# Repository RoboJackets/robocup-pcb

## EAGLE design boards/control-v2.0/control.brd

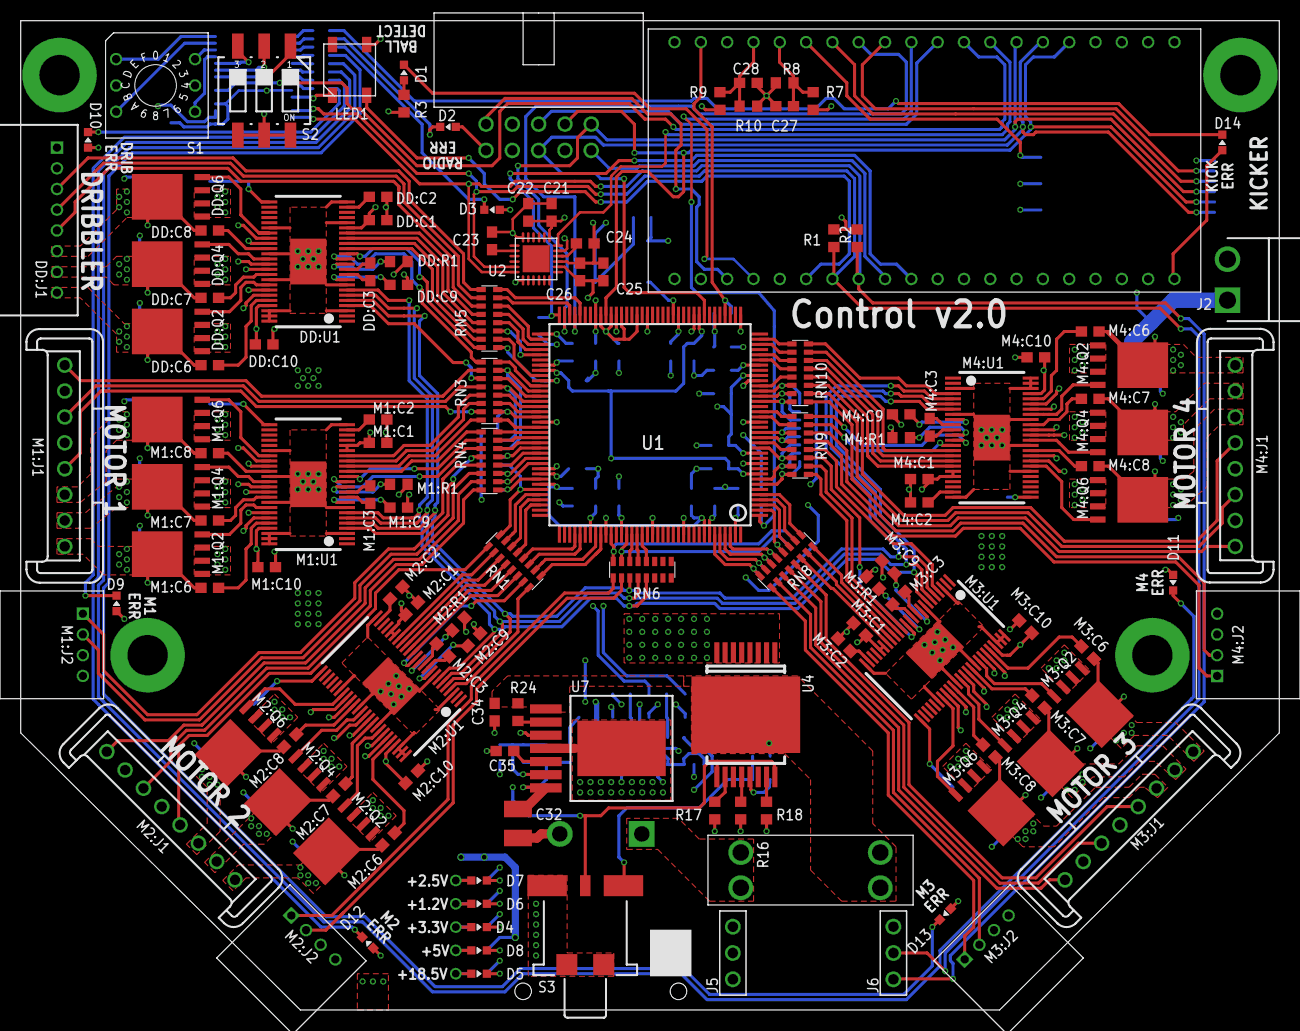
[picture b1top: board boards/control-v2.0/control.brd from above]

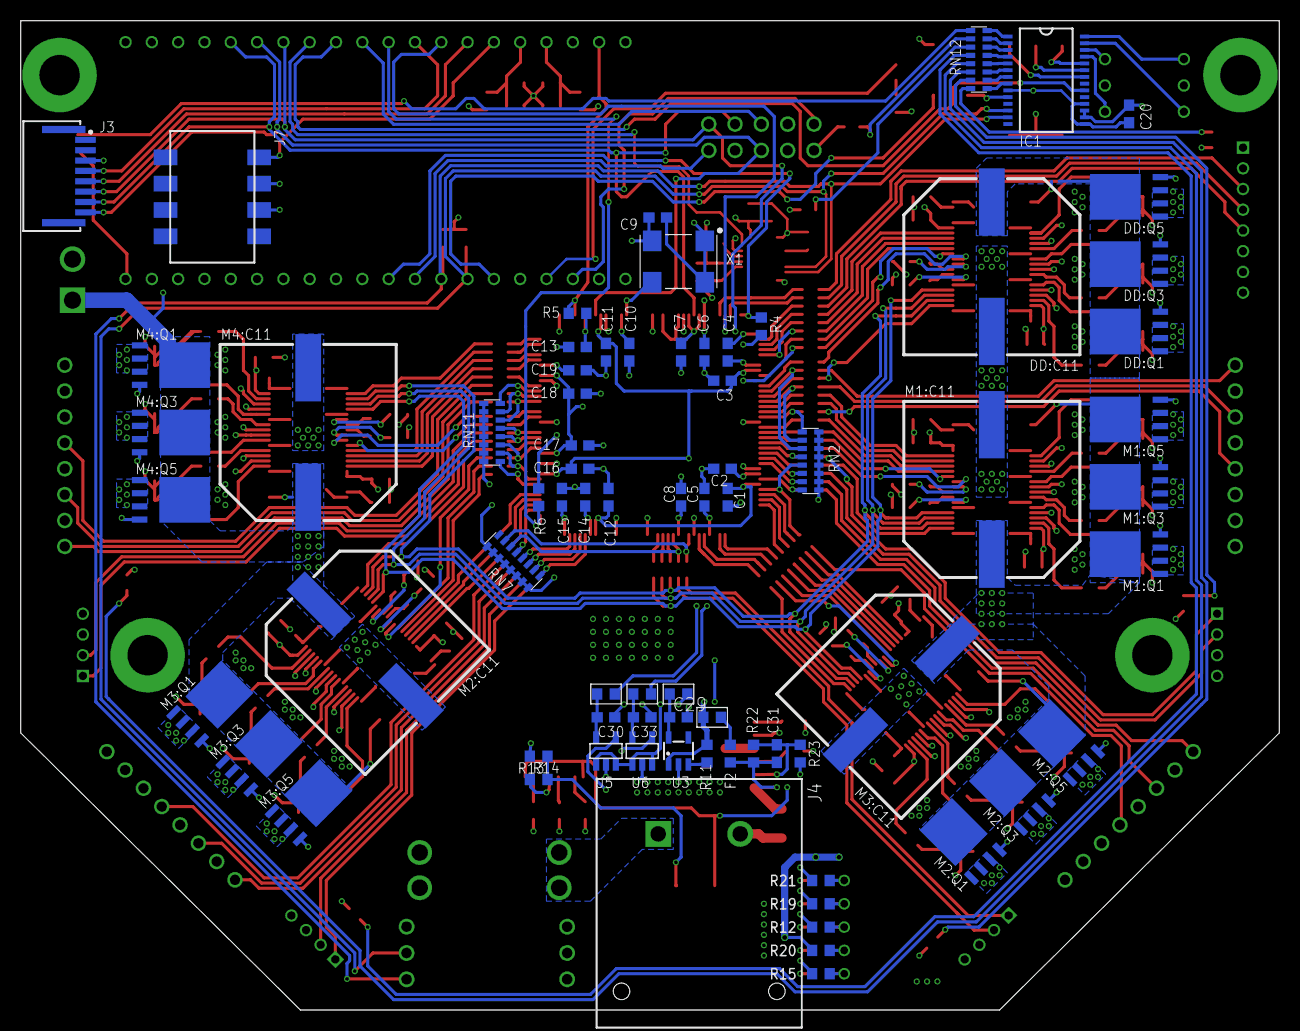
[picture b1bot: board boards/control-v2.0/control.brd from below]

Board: 4 copper layers, 121.5 x 95.5 mm, 206 parts (74 on the bottom side), 284 nets.

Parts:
C1, C2, C3, C4, C5, C6, C7, C8, C9, C10, C11, C12, C13, C14, C15, C16, C17, C18, C19, C20, C24, C27, C28: 0.1uF; C0603
C21, C22, C26: 0.47uF; C0603
C23: 2200pF; C0603
C25: 10000pF; C0603
C29, C30, C33: 1uF; C0603
C31: 0.022uF; C0603
C32: LMK325ABJ107MM-P; C1210
C34: GRM188R6YA106MA73D; C0603
C35: 0.1uF 50V; C0603
D1: BLUE; CHIP-LED0603
D2, D3, D9, D10, D11, D12, D13, D14: RED; CHIP-LED0603
D4, D5, D6, D7, D8: GREEN; CHIP-LED0603
DD:C1, DD:C2: 1uF; C0603
DD:C3: 0.022uF 50V; C0603
DD:C6, DD:C7, DD:C8, DD:C10: 0.1uF 50V; C0603
DD:C9: 2.2uF 50V; C0603
DD:C11: EEE-FK1H102AM; PANASONIC_J16
DD:J1: 8-PIN_2MM-H; 2MM-8-H
DD:Q1, DD:Q2, DD:Q3, DD:Q4, DD:Q5, DD:Q6: IRFH7545; PQFN_5X6_E
DD:R1: 10k; R0603
DD:U1: DRV8303DCA; TSSOP-48_PAD
F1: 30A; 3557-2
F2: 0603L075SLYR; F0603
IC1: MCP23017-E/SS; SSOP-28
J1: SBH11-PBPC-D05-RA; SBH11-*-D05-RA
J2: B2PS-VH(LF)(SN); B2PS-CENTERED
J3: HFW8R-1ST
J4: DF22-2; DF22-2-H
J5, J6: 3-PIN-HEADER
J7: 147721-3
KIT1: MBED_NXP_LPC1768; MBED-KIT
LED1: WS2812B; 5050
M1:C1, M1:C2, M2:C1, M2:C2, M3:C1, M3:C2, M4:C1, M4:C2: 1uF; C0603
M1:C3, M2:C3, M3:C3, M4:C3: 0.022uF 50V; C0603
M1:C6, M1:C7, M1:C8, M1:C10, M2:C6, M2:C7, M2:C8, M2:C10, M3:C6, M3:C7, M3:C8, M3:C10, M4:C6, M4:C7, M4:C8, M4:C10: 0.1uF 50V; C0603
M1:C9, M2:C9, M3:C9, M4:C9: 2.2uF 50V; C0603
M1:C11, M2:C11, M3:C11, M4:C11: EEE-FK1H102AM; PANASONIC_J16
M1:J1, M2:J1, M3:J1, M4:J1: MKS-1658
M1:J2, M2:J2, M3:J2, M4:J2: 4-PIN_2MM-H; 2MM-4-H
M1:Q1, M1:Q2, M1:Q3, M1:Q4, M1:Q5, M1:Q6, M2:Q1, M2:Q2, M2:Q3, M2:Q4, M2:Q5, M2:Q6, M3:Q1, M3:Q2, M3:Q3, M3:Q4, M3:Q5, M3:Q6, M4:Q1, M4:Q2, M4:Q3, M4:Q4, M4:Q5, M4:Q6: IRFH7545; PQFN_5X6_E
M1:R1, M2:R1, M3:R1, M4:R1: 10k; R0603
M1:U1, M2:U1, M3:U1, M4:U1: DRV8303DCA; TSSOP-48_PAD
R1, R2, R5, R6: 4.7k; R0603
R3, R4, R12, R19, R21: 330; R0603
R7: 68k; R0603
R8, R9, R10, R11, R16: 10k; R0603
R13: 270k; R0603
R14, R24: 100k; R0603
R15, R17, R18, R20: 1k; R0603
R22: 34k; R0603
R23: 6.49k; R0603
RN1, RN3, RN4, RN5, RN6, RN8, RN9, RN10: 330; RA-8_2506
RN2, RN7, RN11, RN12: RA-8_2506
S1: 94HCB16T; HEX
S2: 219-03; CTS-219-03
S3: 34EWMSP12M6RT
SB1, SB2, SB3, SB4: SOLDERBRIDGESB0603; SB0603
U1: XC3S250E-4TQG144C; TQFP144
U2: MPU-6050; QFN-24-4MM2
U3: TLV70233DBVR; SOT-23-5
U4: VND5E006ASPTR-E; POWERSO-16
U5: MCP1824T-1202E/OT; SOT-23-5
U6: MCP1824T-2502E/OT; SOT-23-5
U7: LMZ14201; TO-PMOD-7
X1: ASV-18.432MHZ-EJ-T; ASV

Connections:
1.2V-LED: R19.1, U5.4
1.2V-LED-PRE: D6.A, R19.2
2.5V-LED: R21.1, U6.4
2.5V-LED-PRE: D7.A, R21.2
3.3V-EN: R11.1, U3.3
3.3V-LED-PRE: D4.A, R12.1
5V-LED-PRE: D8.A, R20.2
18.5V-LED-PRE: D5.A, R15.1
!CS!-FPGA: KIT1.P$13, U1.69
!CS!-KICK: J3.5, KIT1.P$14
!CS!-RADIO: J1.10, KIT1.P$29
!RST!-KICK: J3.4, KIT1.P$12
!RST!-RADIO: J1.5, KIT1.P$23
+1.2V: C3.1, C5.1, C11.1, C16.1, SB2.2, U1.9, U1.45, U1.80, U1.115
+1.2V-PRE: C30.1, SB2.1, U5.5
+2.5V: C1.1, C6.1, C12.1, C19.1, R4.2, R6.2, SB4.2, U1.30, U1.65, U1.102, U1.137
+2.5V-PRE: C33.1, SB4.1, U6.5
+3.3V: C2.1, C4.1, C7.1, C8.1, C9.1, C10.1, C13.1, C14.1, C15.1, C17.1, C18.1, C20.1, C21.1, C22.1, C25.1, C26.1, D2.A, D3.A, D9.A, D10.A, D11.A, D12.A, D13.A, D14.A, DD:C1.1, DD:C10.1, DD:J1.2, DD:R1.1, DD:U1.19, DD:U1.45, IC1.9, IC1.15, IC1.18, J1.6, J5.2, J7.3, KIT1.VOUT, LED1.1, M1:C1.1, M1:C10.1, M1:R1.1, M1:U1.19, M1:U1.20, M1:U1.45, M2:C1.1, M2:C10.1, M2:R1.1, M2:U1.19, M2:U1.20, M2:U1.45, M3:C1.1, M3:C10.1, M3:R1.1, M3:U1.19, M3:U1.20, M3:U1.45, M4:C1.1, M4:C10.1, M4:R1.1, M4:U1.19, M4:U1.20, M4:U1.45, R1.2, R2.2, R3.2, R5.1, R12.2, SB1.2, U1.13, U1.28, U1.42, U1.49, U1.57, U1.60, U1.62, U1.64, U1.79, U1.100, U1.121, U1.138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
+3.3V-PRE: C29.1, SB1.1, U3.5
+5V: KIT1.VIN, KIT1.VU, M1:J1.4, M1:J2.4, M2:J1.4, M2:J2.4, M3:J1.4, M3:J2.4, M4:J1.4, M4:J2.4, R9.1, R11.2, R20.1, SB3.2, U3.1
+5V-FUSE: C31.1, C32.1, F2.1, R22.2, U7.7
+5V-PRE: F2.2, SB3.1
+18.5V: DD:C11.+, DD:Q1.5678, DD:Q3.5678, DD:Q5.5678, DD:U1.25, J2.1, M1:C11.+, M1:Q1.5678, M1:Q3.5678, M1:Q5.5678, M1:U1.25, M2:C11.+, M2:Q1.5678, M2:Q3.5678, M2:Q5.5678, M2:U1.25, M3:C11.+, M3:Q1.5678, M3:Q3.5678, M3:Q5.5678, M3:U1.25, M4:C11.+, M4:Q1.5678, M4:Q3.5678, M4:Q5.5678, M4:U1.25, R7.1, R15.2, U4.1, U4.2, U4.3, U4.4, U4.5, U4.6, U4.7, U4.8
BALL-DETECT: J7.1, KIT1.P$15
CPOUT: C23.1, U2.20
CS1: R17.2, U4.10
CS2: R18.2, U4.15
CS-DIS: R16.2, U4.12
DD-!CS: DD:U1.4, RN3.11
DD-A-H: DD:U1.13, RN3.9
DD-A-L: DD:U1.14, RN5.16
DD-B-H: DD:U1.15, RN5.15
DD-B-L: DD:U1.16, RN5.14
DD-C-H: DD:U1.17, RN5.13
DD-C-L: DD:U1.18, RN5.12
DD-H1: DD:J1.5, RN5.11
DD-H2: DD:J1.4, RN5.10
DD-H3: DD:J1.3, RN5.9
DD:AVDD: DD:C2.1, DD:U1.23
DD:BST-A: DD:C6.1, DD:U1.44
DD:BST-B: DD:C7.1, DD:U1.39
DD:BST-C: DD:C8.1, DD:U1.34
DD:CP1: DD:C3.1, DD:U1.10
DD:CP2: DD:C3.2, DD:U1.11
DD:EN-GATE: DD:R1.2, DD:U1.12
DD:GH-A: DD:Q1.4, DD:U1.43
DD:GH-B: DD:Q3.4, DD:U1.38
DD:GH-C: DD:Q5.4, DD:U1.33
DD:GL-A: DD:Q2.4, DD:U1.41
DD:GL-B: DD:Q4.4, DD:U1.36
DD:GL-C: DD:Q6.4, DD:U1.31
DD:GVDD: DD:C9.1, DD:U1.9
DD:PHASE-A: DD:C6.2, DD:J1.8, DD:Q1.1, DD:Q1.2, DD:Q1.3, DD:Q2.5678, DD:U1.42
DD:PHASE-B: DD:C7.2, DD:J1.7, DD:Q3.1, DD:Q3.2, DD:Q3.3, DD:Q4.5678, DD:U1.37
DD:PHASE-C: DD:C8.2, DD:J1.6, DD:Q5.1, DD:Q5.2, DD:Q5.3, DD:Q6.5678, DD:U1.32
DIP-1: IC1.22, S2.1
DIP-2: IC1.23, S2.2
DIP-3: IC1.24, S2.3
EN-PWR: S3.2, U4.9, U4.16, U7.3
EN-PWR-PRE: R13.1, R14.2, S3.1
FB: C31.2, R22.1, R23.2, U7.6
FPGA-CLK: U1.50, X1.3
FPGA-DONE: KIT1.P$30, R4.1, U1.72
FPGA-INIT: KIT1.P$19, R5.2, U1.40
FPGA-PROG: KIT1.P$11, R6.1, U1.1
GND: C1.2, C2.2, C3.2, C4.2, C5.2, C6.2, C7.2, C8.2, C9.2, C10.2, C11.2, C12.2, C13.2, C14.2, C15.2, C16.2, C17.2, C18.2, C19.2, C20.2, C21.2, C22.2, C23.2, C24.2, C25.2, C26.2, C27.2, C28.2, C29.2, C30.2, C32.2, C33.2, C34.2, C35.2, D4.C, D5.C, D6.C, D7.C, D8.C, DD:C1.2, DD:C2.2, DD:C9.2, DD:C10.2, DD:C11.-, DD:J1.1, DD:Q2.1, DD:Q2.2, DD:Q2.3, DD:Q4.1, DD:Q4.2, DD:Q4.3, DD:Q6.1, DD:Q6.2, DD:Q6.3, DD:U1.3, DD:U1.8, DD:U1.20, DD:U1.24, DD:U1.30, DD:U1.35, DD:U1.40, DD:U1.46, DD:U1.47, DD:U1.48, DD:U1.PAD, IC1.10, IC1.16, IC1.17, J1.7, J2.2, J3.3, J4.2, J5.1, J7.2, KIT1.GND, LED1.3, M1:C1.2, M1:C2.2, M1:C9.2, M1:C10.2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
GPB0: IC1.1, RN12.8
GPB1: IC1.2, RN12.7
GPB2: IC1.3, RN12.6
GPB3: IC1.4, RN12.5
GPB4: IC1.5, RN12.4
GPB5: IC1.6, RN12.3
GPB6: IC1.7, RN12.2
GPB7: IC1.8, RN12.1
HEX-0: IC1.28, S1.1
HEX-1: IC1.25, S1.2
HEX-2: IC1.27, S1.4
HEX-3: IC1.26, S1.8
INT-IO: IC1.20, KIT1.P$9
INT-MPU: KIT1.P$8, U2.12
INT-RADIO: J1.3, KIT1.P$10
LED-BALL: D1.C, KIT1.P$24
LED-BALL-PRE: D1.A, R3.1
LED-DD: D10.C, RN12.16
LED-KICK: D14.C, RN12.9
LED-M1: D9.C, RN12.15
LED-M2: D12.C, RN12.14
LED-M3: D13.C, RN12.12
LED-M4: D11.C, RN12.13
LED-MPU: D3.C, RN12.11
LED-NEO: KIT1.P$26, LED1.4
LED-RADIO: D2.C, RN12.10
M1-!CS: M1:U1.4, RN4.13
M1-A-H: M1:U1.13, RN4.11
M1-A-L: M1:U1.14, RN4.10
M1-B-H: M1:U1.15, RN4.9
M1-B-L: M1:U1.16, RN3.16
M1-C-H: M1:U1.17, RN3.14
M1-C-L: M1:U1.18, RN3.13
M1-ENC-A: M1:J2.2, RN4.14
M1-ENC-B: M1:J2.1, RN4.12
M1-H1: M1:J1.1, RN3.10
M1-H2: M1:J1.3, RN3.12
M1-H3: M1:J1.5, RN3.15
M1:AVDD: M1:C2.1, M1:U1.23
M1:BST-A: M1:C6.1, M1:U1.44
M1:BST-B: M1:C7.1, M1:U1.39
M1:BST-C: M1:C8.1, M1:U1.34
M1:CP1: M1:C3.1, M1:U1.10
M1:CP2: M1:C3.2, M1:U1.11
M1:EN-GATE: M1:R1.2, M1:U1.12
M1:GH-A: M1:Q1.4, M1:U1.43
M1:GH-B: M1:Q3.4, M1:U1.38
M1:GH-C: M1:Q5.4, M1:U1.33
M1:GL-A: M1:Q2.4, M1:U1.41
M1:GL-B: M1:Q4.4, M1:U1.36
M1:GL-C: M1:Q6.4, M1:U1.31
M1:GVDD: M1:C9.1, M1:U1.9
M1:PHASE-A: M1:C7.2, M1:J1.7, M1:Q3.1, M1:Q3.2, M1:Q3.3, M1:Q4.5678, M1:U1.37
M1:PHASE-B: M1:C6.2, M1:J1.8, M1:Q1.1, M1:Q1.2, M1:Q1.3, M1:Q2.5678, M1:U1.42
M1:PHASE-C: M1:C8.2, M1:J1.6, M1:Q5.1, M1:Q5.2, M1:Q5.3, M1:Q6.5678, M1:U1.32
M2-A-H: M2:U1.13, RN1.15
M2-A-L: M2:U1.14, RN1.14
M2-B-H: M2:U1.15, RN1.13
M2-B-L: M2:U1.16, RN1.12
M2-C-H: M2:U1.17, RN1.11
M2-C-L: M2:U1.18, RN1.10
M2-ENC-A: M2:J2.2, RN6.10
M2-ENC-B: M2:J2.1, RN6.9
M2-H1: M2:J1.1, RN4.15
M2-H2: M2:J1.3, RN4.16
M2-H3: M2:J1.5, RN1.9
M2:AVDD: M2:C2.1, M2:U1.23
M2:BST-A: M2:C6.1, M2:U1.44
M2:BST-B: M2:C7.1, M2:U1.39
M2:BST-C: M2:C8.1, M2:U1.34
M2:CP1: M2:C3.1, M2:U1.10
M2:CP2: M2:C3.2, M2:U1.11
M2:EN-GATE: M2:R1.2, M2:U1.12
M2:GH-A: M2:Q1.4, M2:U1.43
M2:GH-B: M2:Q3.4, M2:U1.38
M2:GH-C: M2:Q5.4, M2:U1.33
M2:GL-A: M2:Q2.4, M2:U1.41
M2:GL-B: M2:Q4.4, M2:U1.36
M2:GL-C: M2:Q6.4, M2:U1.31
M2:GVDD: M2:C9.1, M2:U1.9
M2:PHASE-A: M2:C7.2, M2:J1.7, M2:Q3.1, M2:Q3.2, M2:Q3.3, M2:Q4.5678, M2:U1.37
M2:PHASE-B: M2:C6.2, M2:J1.8, M2:Q1.1, M2:Q1.2, M2:Q1.3, M2:Q2.5678, M2:U1.42
M2:PHASE-C: M2:C8.2, M2:J1.6, M2:Q5.1, M2:Q5.2, M2:Q5.3, M2:Q6.5678, M2:U1.32
M3-!CS: M3:U1.4, RN9.12
M3-A-H: M3:U1.13, RN9.11
M3-A-L: M3:U1.14, RN9.10
M3-B-H: M3:U1.15, RN9.9
M3-B-L: M3:U1.16, RN8.16
M3-C-H: M3:U1.17, RN8.15
M3-C-L: M3:U1.18, RN8.14
M3-ENC-A: M3:J2.2, RN8.10
M3-ENC-B: M3:J2.1, RN8.9
M3-H1: M3:J1.1, RN8.11
M3-H2: M3:J1.3, RN8.12
M3-H3: M3:J1.5, RN8.13
M3:AVDD: M3:C2.1, M3:U1.23
M3:BST-A: M3:C6.1, M3:U1.44
M3:BST-B: M3:C7.1, M3:U1.39
M3:BST-C: M3:C8.1, M3:U1.34
M3:CP1: M3:C3.1, M3:U1.10
M3:CP2: M3:C3.2, M3:U1.11
M3:EN-GATE: M3:R1.2, M3:U1.12
M3:GH-A: M3:Q1.4, M3:U1.43
M3:GH-B: M3:Q3.4, M3:U1.38
M3:GH-C: M3:Q5.4, M3:U1.33
M3:GL-A: M3:Q2.4, M3:U1.41
M3:GL-B: M3:Q4.4, M3:U1.36
M3:GL-C: M3:Q6.4, M3:U1.31
M3:GVDD: M3:C9.1, M3:U1.9
M3:PHASE-A: M3:C7.2, M3:J1.7, M3:Q3.1, M3:Q3.2, M3:Q3.3, M3:Q4.5678, M3:U1.37
M3:PHASE-B: M3:C6.2, M3:J1.8, M3:Q1.1, M3:Q1.2, M3:Q1.3, M3:Q2.5678, M3:U1.42
M3:PHASE-C: M3:C8.2, M3:J1.6, M3:Q5.1, M3:Q5.2, M3:Q5.3, M3:Q6.5678, M3:U1.32
M4-!CS: M4:U1.4, RN10.16
M4-A-H: M4:U1.13, RN9.16
M4-A-L: M4:U1.14, RN9.15
M4-B-H: M4:U1.15, RN10.15
M4-B-L: M4:U1.16, RN10.14
M4-C-H: M4:U1.17, RN10.13
M4-C-L: M4:U1.18, RN10.12
M4-ENC-A: M4:J2.2, RN9.14
M4-ENC-B: M4:J2.1, RN9.13
M4-H1: M4:J1.1, RN10.9
M4-H2: M4:J1.3, RN10.10
M4-H3: M4:J1.5, RN10.11
M4:AVDD: M4:C2.1, M4:U1.23
M4:BST-A: M4:C6.1, M4:U1.44
M4:BST-B: M4:C7.1, M4:U1.39
M4:BST-C: M4:C8.1, M4:U1.34
M4:CP1: M4:C3.1, M4:U1.10
M4:CP2: M4:C3.2, M4:U1.11
M4:EN-GATE: M4:R1.2, M4:U1.12
M4:GH-A: M4:Q1.4, M4:U1.43
M4:GH-B: M4:Q3.4, M4:U1.38
M4:GH-C: M4:Q5.4, M4:U1.33
M4:GL-A: M4:Q2.4, M4:U1.41
M4:GL-B: M4:Q4.4, M4:U1.36
M4:GL-C: M4:Q6.4, M4:U1.31
M4:GVDD: M4:C9.1, M4:U1.9
M4:PHASE-A: M4:C7.2, M4:J1.7, M4:Q3.1, M4:Q3.2, M4:Q3.3, M4:Q4.5678, M4:U1.37
M4:PHASE-B: M4:C6.2, M4:J1.8, M4:Q1.1, M4:Q1.2, M4:Q1.3, M4:Q2.5678, M4:U1.42
M4:PHASE-C: M4:C8.2, M4:J1.6, M4:Q5.1, M4:Q5.2, M4:Q5.3, M4:Q6.5678, M4:U1.32
MISO: J1.8, J3.8, KIT1.P$6, U1.44
MISO-AUX: DD:U1.6, M1:U1.6, M2:U1.6, M3:U1.6, M4:U1.6, RN6.12
MOSI: J1.2, J3.7, KIT1.P$5, U1.63
MOSI-AUX: DD:U1.5, M1:U1.5, M2:U1.5, M3:U1.5, M4:U1.5, RN6.11
R-P1: RN5.1, U1.82
R-P2: RN5.2, U1.81
R-P3: RN5.3, U1.77
R-P4: RN5.4, U1.76
R-P5: RN5.5, U1.75
R-P6: RN5.6, U1.74
R-P7: RN5.7, U1.70
R-P8: RN5.8, U1.68
R-P9: RN3.1, U1.91
R-P10: RN2.1, RN3.2, U1.89
R-P11: RN3.3, U1.88
R-P12: RN3.4, U1.87
R-P13: RN2.2, RN3.5, U1.86
R-P14: RN3.6, U1.85
R-P15: RN2.3, RN3.7, U1.84
R-P16: RN3.8, U1.83
R-P17: RN2.8, RN4.1, U1.101
R-P18: RN2.7, RN4.2, U1.98
R-P19: RN2.6, RN4.3, U1.97
R-P20: RN4.4, U1.96
R-P21: RN2.4, RN4.5, U1.95
R-P22: RN4.6, U1.94
R-P23: RN4.7, U1.93
R-P24: RN4.8, U1.92
R-P25: RN1.1, U1.117
R-P26: RN1.2, U1.116
R-P27: RN1.3, U1.113
R-P28: RN1.4, U1.112
R-P29: RN1.5, U1.106
R-P30: RN1.6, U1.105
R-P31: RN1.7, U1.104
R-P32: RN1.8, RN2.5, U1.103
R-P36: RN6.4, U1.125
R-P37: RN6.5, U1.124
R-P38: RN6.6, U1.123
R-P39: RN6.7, RN7.6, U1.122
R-P40: RN6.8, RN7.7, U1.119
R-P41: RN8.1, U1.5
R-P42: RN8.2, U1.4
R-P43: RN8.3, U1.3
R-P44: RN7.5, RN8.4, U1.2
R-P45: RN7.4, RN8.5, U1.142
R-P46: RN7.3, RN8.6, U1.141
R-P47: RN7.2, RN8.7, U1.140
R-P48: RN7.1, RN8.8, U1.139
R-P49: RN9.1, U1.21
R-P50: RN9.2, U1.20
R-P51: RN9.3, RN11.5, U1.17
R-P52: RN9.4, RN11.4, U1.16
R-P53: RN9.5, U1.15
R-P54: RN9.6, RN11.3, U1.14
R-P55: RN9.7, RN11.2, U1.8
R-P56: RN9.8, RN11.1, U1.7
R-P57: RN10.1, U1.35
R-P58: RN10.2, U1.34
R-P59: RN10.3, U1.32
R-P60: RN10.4, U1.31
R-P61: RN10.5, U1.26
R-P62: RN10.6, RN11.8, U1.25
R-P63: RN10.7, RN11.7, U1.24
R-P64: RN10.8, RN11.6, U1.23
REGOUT: C24.1, U2.10
RON: R24.2, U7.2
SCK: J1.1, J3.6, KIT1.P$7, U1.71
SCK-AUX: DD:U1.7, M1:U1.7, M2:U1.7, M3:U1.7, M4:U1.7, RN6.13
SCL: IC1.12, J6.2, KIT1.P$27, R1.1, U2.23
SDA: IC1.13, J6.1, KIT1.P$28, R2.1, U2.24
SENSE-BATT: C27.1, KIT1.P$16, R7.2, R8.1
SENSE-VIN: C28.1, KIT1.P$17, R9.2, R10.1
SS: C35.1, U7.5
VBATT: C34.1, F1.3, F1.4, R13.2, R24.1, U4.17, U7.1
VIN: F1.1, F1.2, J4.1
WD2-!CS: M2:U1.4, RN1.16

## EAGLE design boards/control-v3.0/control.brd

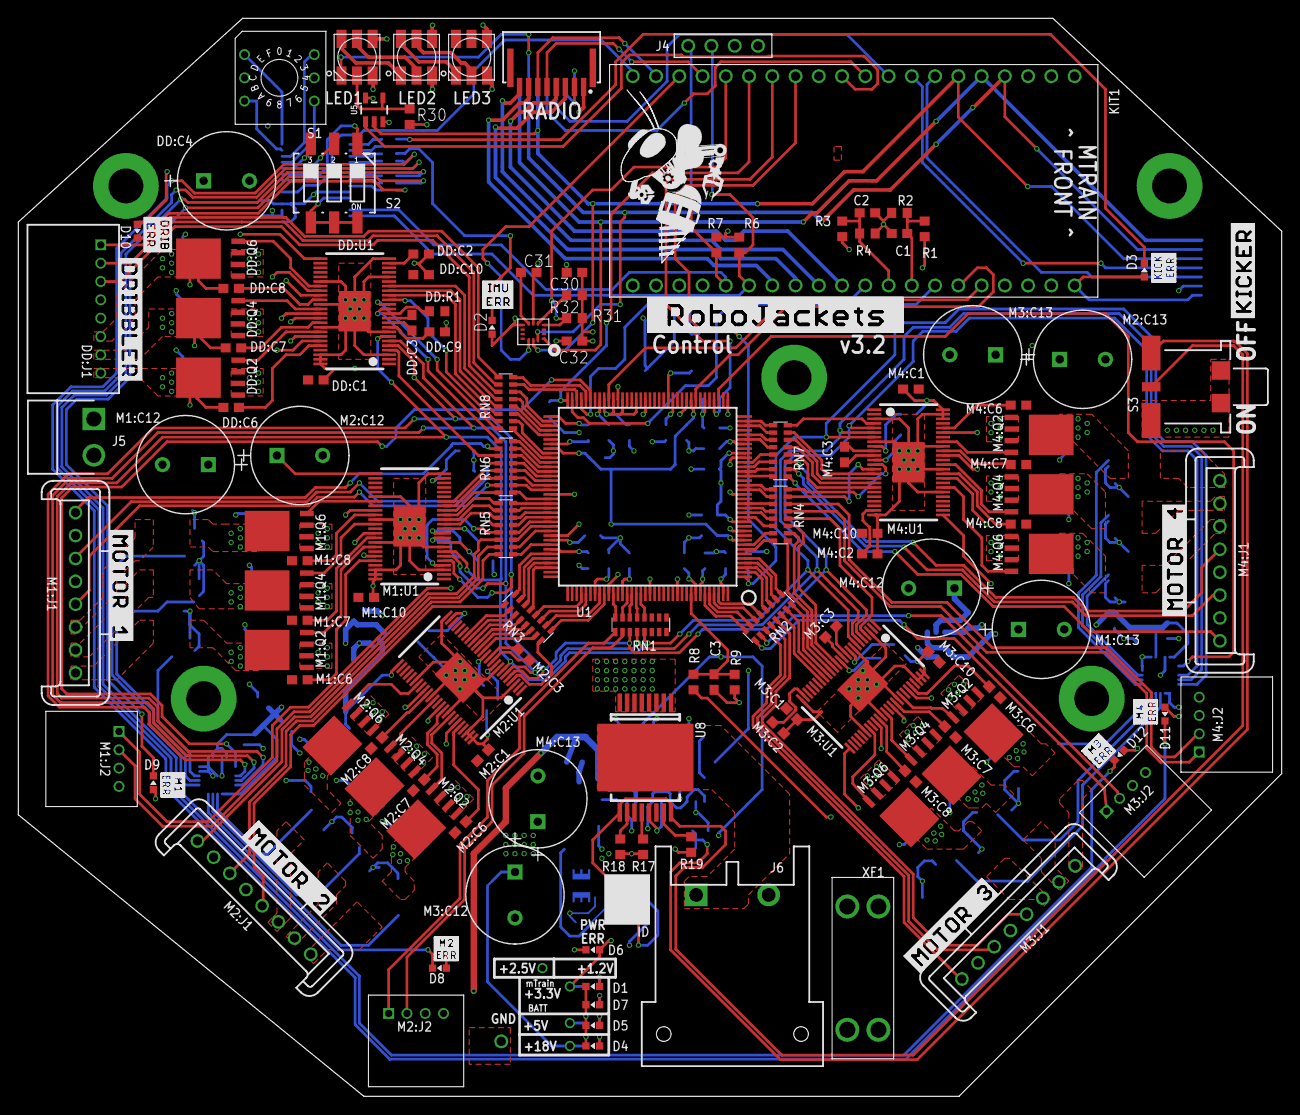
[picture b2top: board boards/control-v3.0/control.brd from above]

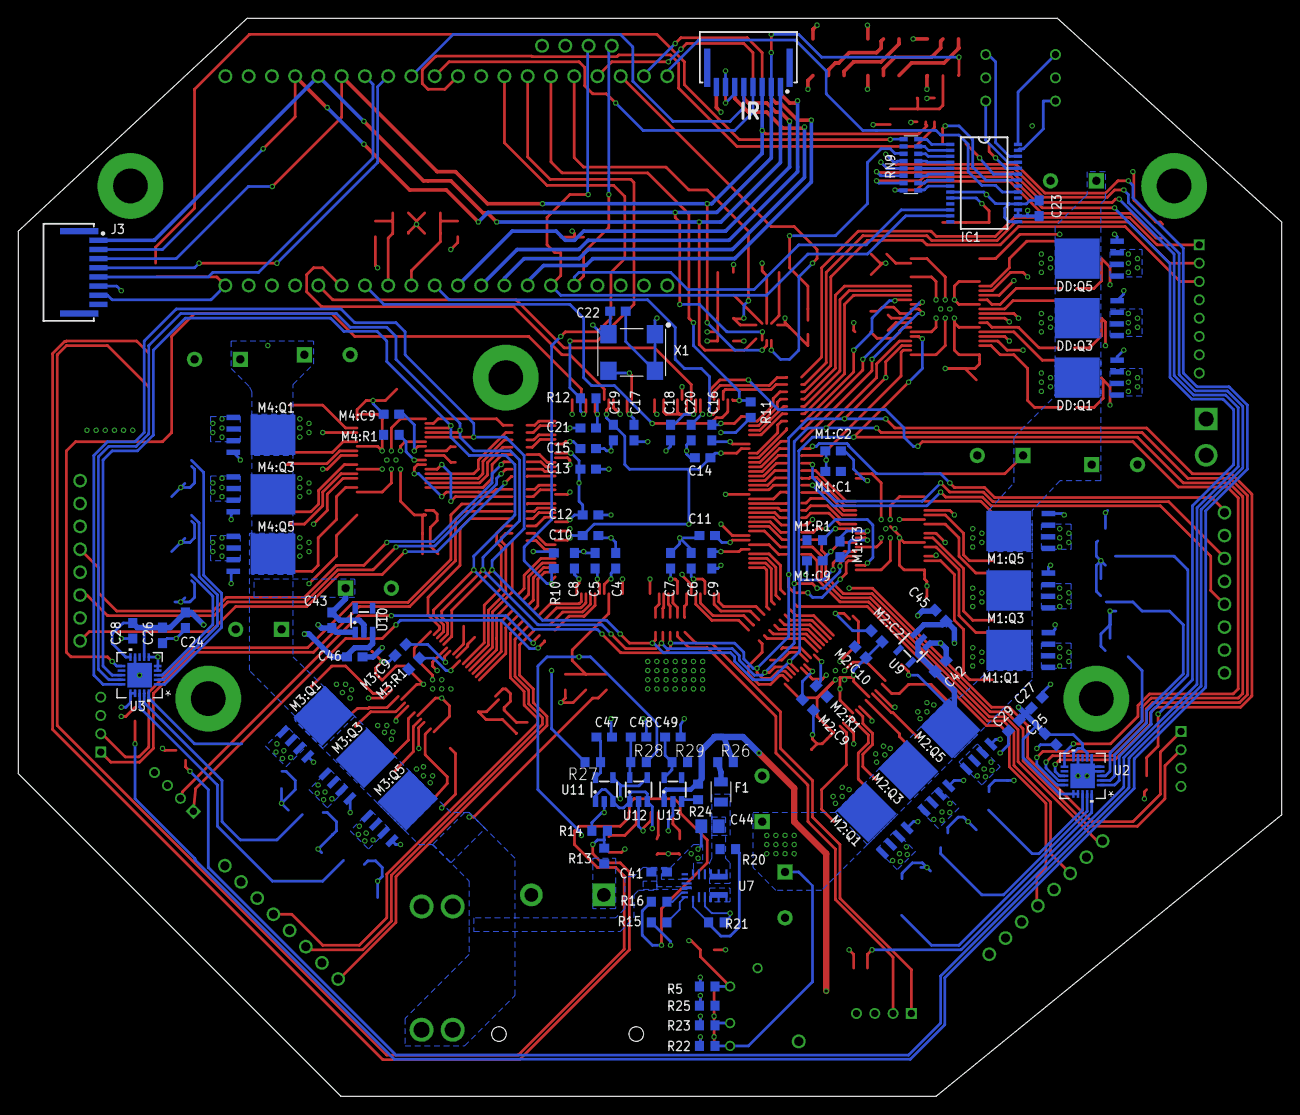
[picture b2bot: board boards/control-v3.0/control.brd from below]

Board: 6 copper layers, 138.0 x 117.8 mm, 236 parts (95 on the bottom side), 301 nets.

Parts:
C1, C42, C43: 0.1uF 50V; C0603
C2, C3, C4, C5, C6, C7, C8, C9, C10, C11, C12, C13, C14, C15, C16, C17, C18, C19, C20, C21, C22, C23, C26, C27, C28, C29, C30, C31, C32: 0.1uF; C0603
C24, C25: 10uF; C0603
C41: GRM188R6YA106MA73D; C0603
C44: 22uF 16V; C0805
C45, C46, C47, C48, C49: 1uF; C0603
D1, D4, D5, D7: GREEN; CHIP-LED0603
D2, D3, D6, D8, D9, D10, D11, D12: RED; CHIP-LED0603
DD:C1, DD:C2: 1uF; C0603
DD:C3: 0.022uF 50V; C0603
DD:C4: ECA-1HHG221; CAP_PAN_10X12.5
DD:C6, DD:C7, DD:C8, DD:C10: 0.1uF 50V; C0603
DD:C9: 2.2uF 50V; C0603
DD:J1: 8-PIN_2MM-H; 2MM-8-H
DD:Q1, DD:Q2, DD:Q3, DD:Q4, DD:Q5, DD:Q6: IRFH7545; PQFN_5X6_E
DD:R1: 10k; R0603
DD:U1: DRV8303DCA; TSSOP-48_PAD
F1: 0805L200SLTHYR; FUSC2113X75
IC1: MCP23017-E/SS; SSOP-28
IR: HFW8R-1ST
J3: HFW8R-1ST
J4: 4-PIN-HEADER
J5: B2PS-VH(LF)(SN); B2PS-CENTERED
J6: DF22-2; DF22-2-H
KIT1: MTRAIN; MTRAIN-KIT
LED1, LED2, LED3: APA102C-5050; APA102_5050
M1:C1, M1:C2, M2:C1, M2:C2, M3:C1, M3:C2, M4:C1, M4:C2: 1uF; C0603
M1:C3, M2:C3, M3:C3, M4:C3: 0.022uF 50V; C0603
M1:C6, M1:C7, M1:C8, M1:C10, M2:C6, M2:C7, M2:C8, M2:C10, M3:C6, M3:C7, M3:C8, M3:C10, M4:C6, M4:C7, M4:C8, M4:C10: 0.1uF 50V; C0603
M1:C9, M2:C9, M3:C9, M4:C9: 2.2uF 50V; C0603
M1:C12, M1:C13, M2:C12, M2:C13, M3:C12, M3:C13, M4:C12, M4:C13: ECA-1HHG221; CAP_PAN_10X12.5
M1:J1, M2:J1, M3:J1, M4:J1: MKS-1658
M1:J2, M2:J2, M3:J2, M4:J2: 4-PIN_2MM-H; 2MM-4-H
M1:Q1, M1:Q2, M1:Q3, M1:Q4, M1:Q5, M1:Q6, M2:Q1, M2:Q2, M2:Q3, M2:Q4, M2:Q5, M2:Q6, M3:Q1, M3:Q2, M3:Q3, M3:Q4, M3:Q5, M3:Q6, M4:Q1, M4:Q2, M4:Q3, M4:Q4, M4:Q5, M4:Q6: IRFH7545; PQFN_5X6_E
M1:R1, M2:R1, M3:R1, M4:R1: 10k; R0603
M1:U1, M2:U1, M3:U1, M4:U1: DRV8303DCA; TSSOP-48_PAD
R1, R8: 68k; R0603
R2, R3, R4, R9, R17, R24, R31: 10k; R0603
R5, R11, R25: 330; R0603
R6, R7, R10, R12: 4.7k; R0603
R13: 270k; R0603
R14: 100k; R0603
R15: 43.2k; R0603
R16: 150k; R0603
R18, R19, R22, R23: 1k; R0603
R20: 160k 1%; R0603
R21: 30.1k 1%; R0603
R26, R27, R28, R29: 0k; R0603
R30: 50k; R0603
R32: 0; R0603
RADIO: HFW8R-1ST
RN1, RN2, RN3, RN4, RN5, RN6, RN7, RN8, RN9: 330; RA-8_2506
S1: 94HCB16T; HEX
S2: 219-03; CTS-219-03
S3: 34EWMSP12M6RT
U1: XC3S250E-4TQG144C; TQFP144
U2, U3: ADS8028IRTJT; RTJ20_2P7X2P7
U4: ICM-42605; ICM-442605-2530091
U5: SN74AHC1G125; SOT23-5
U7: MPM3620GQV-P
U8: VND5E006ASPTR-E; POWERSO-16
U9, U10: TLV70450; SOT-23-5
U11: MCP1824T-1202E/OT; SOT-23-5
U12: MCP1824T-2502E/OT; SOT-23-5
U13: TLV70233DBVR; SOT-23-5
U$1: ERR-DRIB
U$2: ROBOJACKETS
U$3: MOTOR-1
U$4: DRIBBLER
U$5: MOTOR-2
U$6: MOTOR-3
U$7: MOTOR-4
U$8: ERR-M1
U$9: KICKER
U$10: ERR-IMU
U$11: ROBOBUZZ_1.0X2
U$12: ERR-M2
U$13: ERR-M3
U$14: ERR-M4
U$15: ERR-KICK
X1: ASV-18.432MHZ-EJ-T; ASV
XF1: 30A; 3557-2

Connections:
3.3V-EN: R24.1, U13.3
3V3-LED: D7.A, R25.1
5V-LED: D5.A, R23.2
18.5V-LED: D4.A, R22.1
!CS!-ADC1: U1.67, U2.11
!CS!-ADC2: U1.39, U3.11
!CS!-DOT: KIT1.P$11, U5.1
!CS!-FPGA: KIT1.P$31, U1.69
!CS!-ICM: KIT1.P$18, U4.P$12
!CS!-IR: IR.4, KIT1.P$10
!CS!-KICK: J3.4, KIT1.P$8
!CS!-RAD0: KIT1.P$17, RADIO.5
!RST!-IR: IR.5, KIT1.P$9
!RST!-KICK: J3.5, KIT1.P$7
!RST!-RADIO: KIT1.P$19, RADIO.6
+1.2V: C6.1, C10.1, C14.1, C19.1, R27.2, U1.9, U1.45, U1.80, U1.115
+1.2V-PRE: C47.1, R27.1, U11.5
+2.5V: C4.1, C9.1, C15.1, C20.1, R10.2, R11.2, R28.2, U1.30, U1.65, U1.102, U1.137
+2.5V-PRE: C48.1, R28.1, U12.5
+3.3V: C5.1, C7.1, C8.1, C11.1, C12.1, C13.1, C16.1, C17.1, C18.1, C21.1, C22.1, C23.1, C30.1, C32.1, D2.A, D3.A, D6.A, D8.A, D9.A, D10.A, D11.A, D12.A, DD:C1.1, DD:C10.1, DD:R1.1, DD:U1.19, DD:U1.45, IC1.9, IC1.15, IC1.18, IR.7, J3.7, J4.2, KIT1.VDD, R5.1, R6.2, R7.2, R12.1, R25.2, R29.2, R31.2, R32.1, U1.13, U1.28, U1.42, U1.49, U1.57, U1.60, U1.62, U1.64, U1.79, U1.100, U1.121, U1.138, U1.143, U4.P$8, U5.5, U11.1, U11.3, U12.1, U12.3, X1.1, X1.4
+3V3-PRE: C49.1, R29.1, U13.5
+5V: DD:J1.5, KIT1.VIN, LED1.1, LED2.1, LED3.1, M1:J1.4, M1:J2.4, M2:J1.4, M2:J2.4, M3:J1.4, M3:J2.4, M4:J1.4, M4:J2.4, R3.1, R23.1, R24.2, R26.2, RADIO.1, U13.1
+5V-FUSE: C44.1, F1.1, R20.2, U7.789
+18.5V: C41.1, C42.1, C43.1, DD:C4.1, DD:Q1.5678, DD:Q3.5678, DD:Q5.5678, DD:U1.25, M1:C12.1, M1:C13.1, M1:Q1.5678, M1:Q3.5678, M1:Q5.5678, M1:U1.25, M2:C12.1, M2:C13.1, M2:Q1.5678, M2:Q3.5678, M2:Q5.5678, M2:U1.25, M3:C12.1, M3:C13.1, M3:Q1.5678, M3:Q3.5678, M3:Q5.5678, M3:U1.25, M4:C12.1, M4:C13.1, M4:Q1.5678, M4:Q3.5678, M4:Q5.5678, M4:U1.25, R1.1, R8.1, R22.2, U7.16, U9.2, U10.2, XF1.3, XF1.4
AAM: R15.2, U7.18
ADC1-5V: C25.1, C27.1, C29.1, C45.1, U2.7, U2.10, U2.16, U2.17, U9.3
ADC2-5V: C24.1, C26.1, C28.1, C46.1, U3.7, U3.10, U3.16, U3.17, U10.3
BATT-FPGA: C3.1, R8.2, R9.1, U1.136
CS1: R18.2, U8.10
CS2: R19.2, U8.15
CS-DIS: R17.2, U8.12
DD-!CS: DD:U1.4, RN6.11
DD-A-H: DD:U1.13, RN6.9
DD-A-L: DD:U1.14, RN8.16
DD-B-H: DD:U1.15, RN8.15
DD-B-L: DD:U1.16, RN8.14
DD-C-H: DD:U1.17, RN8.13
DD-C-L: DD:U1.18, RN8.12
DD-H1: DD:J1.3, RN8.11
DD-H2: DD:J1.2, RN8.10
DD-H3: DD:J1.1, RN8.9
DD:AVDD: DD:C2.1, DD:U1.23
DD:BST-A: DD:C6.1, DD:U1.44
DD:BST-B: DD:C7.1, DD:U1.39
DD:BST-C: DD:C8.1, DD:U1.34
DD:CP1: DD:C3.1, DD:U1.10
DD:CP2: DD:C3.2, DD:U1.11
DD:EN-GATE: DD:R1.2, DD:U1.12
DD:GH-A: DD:Q1.4, DD:U1.43
DD:GH-B: DD:Q3.4, DD:U1.38
DD:GH-C: DD:Q5.4, DD:U1.33
DD:GL-A: DD:Q2.4, DD:U1.41
DD:GL-B: DD:Q4.4, DD:U1.36
DD:GL-C: DD:Q6.4, DD:U1.31
DD:GVDD: DD:C9.1, DD:U1.9
DD:PHASE-A: DD:C6.2, DD:J1.8, DD:Q1.1, DD:Q1.2, DD:Q1.3, DD:Q2.5678, DD:U1.42
DD:PHASE-B: DD:C7.2, DD:J1.7, DD:Q3.1, DD:Q3.2, DD:Q3.3, DD:Q4.5678, DD:U1.37
DD:PHASE-C: DD:C8.2, DD:J1.6, DD:Q5.1, DD:Q5.2, DD:Q5.3, DD:Q6.5678, DD:U1.32
DIP-1: IC1.22, S2.1
DIP-2: IC1.23, S2.2
DIP-3: IC1.24, S2.3
DOT-CLK-1-2: LED1.2, LED2.5
DOT-CLK-2-3: LED2.2, LED3.5
DOT-MOSI-1-2: LED1.3, LED2.4
DOT-MOSI-2-3: LED2.3, LED3.4
EN: R16.2, U7.17
EN-PWR: R16.1, S3.2, U8.9, U8.16
EN-PWR-PRE: R13.1, R14.2, S3.1
FB: R20.1, R21.2, U7.1
FPGA-CLK: U1.50, X1.3
FPGA-DONE: KIT1.P$15, R11.1, U1.72
FPGA-INIT: KIT1.P$14, R12.2, U1.40
FPGA-PROG: KIT1.P$13, R10.1, U1.1
GND: C1.2, C2.2, C3.2, C4.2, C5.2, C6.2, C7.2, C8.2, C9.2, C10.2, C11.2, C12.2, C13.2, C14.2, C15.2, C16.2, C17.2, C18.2, C19.2, C20.2, C21.2, C22.2, C23.2, C24.2, C25.2, C26.2, C27.2, C28.2, C29.2, C30.2, C31.2, C32.2, C41.2, C42.2, C43.2, C44.2, C45.2, C46.2, C47.2, C48.2, C49.2, D1.C, D4.C, D5.C, D7.C, DD:C1.2, DD:C2.2, DD:C4.2, DD:C9.2, DD:C10.2, DD:J1.4, DD:Q2.1, DD:Q2.2, DD:Q2.3, DD:Q4.1, DD:Q4.2, DD:Q4.3, DD:Q6.1, DD:Q6.2, DD:Q6.3, DD:U1.3, DD:U1.8, DD:U1.20, DD:U1.24, DD:U1.30, DD:U1.35, DD:U1.40, DD:U1.46, DD:U1.47, DD:U1.48, DD:U1.PAD, IC1.10, IC1.16, IC1.17, IR.6, J3.6, J4.1, J5.2, J6.2, KIT1.GND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
GPB0: IC1.1, RN9.8
GPB1: IC1.2, RN9.7
GPB2: IC1.3, RN9.6
GPB3: IC1.4, RN9.5
GPB4: IC1.5, RN9.4
GPB5: IC1.6, RN9.3
GPB6: IC1.7, RN9.2
GPB7: IC1.8, RN9.1
HEX-0: IC1.28, S1.1
HEX-1: IC1.25, S1.2
HEX-2: IC1.27, S1.4
HEX-3: IC1.26, S1.8
INT-ICM: KIT1.P$16, R31.1, U4.P$4
INT-IO: IC1.20, KIT1.P$20
INT-RAD0: KIT1.P$30, RADIO.4
LED-DD: D10.C, RN9.16
LED-ICM: D2.C, RN9.11
LED-KICK: D3.C, RN9.9
LED-M1: D9.C, RN9.15
LED-M2: D8.C, RN9.14
LED-M3: D12.C, RN9.13
LED-M4: D11.C, RN9.12
M1-!CS: M1:U1.4, RN5.13
M1-A-H: M1:U1.15, RN5.9
M1-A-L: M1:U1.16, RN6.16
M1-B-H: M1:U1.13, RN5.11
M1-B-L: M1:U1.14, RN5.10
M1-C-H: M1:U1.17, RN6.14
M1-C-L: M1:U1.18, RN6.13
M1-ENC-A: M1:J2.2, RN5.14
M1-ENC-B: M1:J2.1, RN5.12
M1-H1: M1:J1.1, RN6.10
M1-H2: M1:J1.3, RN6.12
M1-H3: M1:J1.5, RN6.15
M1:+3.3V: M1:C1.1, M1:C10.1, M1:R1.1, M1:U1.19, M1:U1.20, M1:U1.45
M1:AVDD: M1:C2.1, M1:U1.23
M1:BST-A: M1:C6.1, M1:U1.44
M1:BST-B: M1:C7.1, M1:U1.39
M1:BST-C: M1:C8.1, M1:U1.34
M1:CP1: M1:C3.1, M1:U1.10
M1:CP2: M1:C3.2, M1:U1.11
M1:EN-GATE: M1:R1.2, M1:U1.12
M1:GH-A: M1:Q1.4, M1:U1.43
M1:GH-B: M1:Q3.4, M1:U1.38
M1:GH-C: M1:Q5.4, M1:U1.33
M1:GL-A: M1:Q2.4, M1:U1.41
M1:GL-B: M1:Q4.4, M1:U1.36
M1:GL-C: M1:Q6.4, M1:U1.31
M1:GVDD: M1:C9.1, M1:U1.9
M1:PHASE-A: M1:C7.2, M1:J1.7, M1:Q3.1, M1:Q3.2, M1:Q3.3, M1:Q4.5678, M1:U1.37
M1:PHASE-B: M1:C6.2, M1:J1.8, M1:Q1.1, M1:Q1.2, M1:Q1.3, M1:Q2.5678, M1:U1.42
M1:PHASE-C: M1:C8.2, M1:J1.6, M1:Q5.1, M1:Q5.2, M1:Q5.3, M1:Q6.5678, M1:U1.32
M2-!CS: M2:U1.4, RN3.16
M2-A-H: M2:U1.15, RN3.13
M2-A-L: M2:U1.16, RN3.12
M2-B-H: M2:U1.13, RN3.15
M2-B-L: M2:U1.14, RN3.14
M2-C-H: M2:U1.17, RN3.11
M2-C-L: M2:U1.18, RN3.10
M2-ENC-A: M2:J2.2, RN1.10
M2-ENC-B: M2:J2.1, RN1.9
M2-H1: M2:J1.1, RN5.15
M2-H2: M2:J1.3, RN5.16
M2-H3: M2:J1.5, RN3.9
M2:+3.3V: M2:C1.1, M2:C10.1, M2:R1.1, M2:U1.19, M2:U1.20, M2:U1.45
M2:AVDD: M2:C2.1, M2:U1.23
M2:BST-A: M2:C6.1, M2:U1.44
M2:BST-B: M2:C7.1, M2:U1.39
M2:BST-C: M2:C8.1, M2:U1.34
M2:CP1: M2:C3.1, M2:U1.10
M2:CP2: M2:C3.2, M2:U1.11
M2:EN-GATE: M2:R1.2, M2:U1.12
M2:GH-A: M2:Q1.4, M2:U1.43
M2:GH-B: M2:Q3.4, M2:U1.38
M2:GH-C: M2:Q5.4, M2:U1.33
M2:GL-A: M2:Q2.4, M2:U1.41
M2:GL-B: M2:Q4.4, M2:U1.36
M2:GL-C: M2:Q6.4, M2:U1.31
M2:GVDD: M2:C9.1, M2:U1.9
M2:PHASE-A: M2:C7.2, M2:J1.7, M2:Q3.1, M2:Q3.2, M2:Q3.3, M2:Q4.5678, M2:U1.37
M2:PHASE-B: M2:C6.2, M2:J1.8, M2:Q1.1, M2:Q1.2, M2:Q1.3, M2:Q2.5678, M2:U1.42
M2:PHASE-C: M2:C8.2, M2:J1.6, M2:Q5.1, M2:Q5.2, M2:Q5.3, M2:Q6.5678, M2:U1.32
M3-!CS: M3:U1.4, RN4.12
M3-A-H: M3:U1.15, RN4.9
M3-A-L: M3:U1.16, RN2.16
M3-B-H: M3:U1.13, RN4.11
M3-B-L: M3:U1.14, RN4.10
M3-C-H: M3:U1.17, RN2.15
M3-C-L: M3:U1.18, RN2.14
M3-ENC-A: M3:J2.2, RN2.10
M3-ENC-B: M3:J2.1, RN2.9
M3-H1: M3:J1.1, RN2.11
M3-H2: M3:J1.3, RN2.12
M3-H3: M3:J1.5, RN2.13
M3:+3.3V: M3:C1.1, M3:C10.1, M3:R1.1, M3:U1.19, M3:U1.20, M3:U1.45
M3:AVDD: M3:C2.1, M3:U1.23
M3:BST-A: M3:C6.1, M3:U1.44
M3:BST-B: M3:C7.1, M3:U1.39
M3:BST-C: M3:C8.1, M3:U1.34
M3:CP1: M3:C3.1, M3:U1.10
M3:CP2: M3:C3.2, M3:U1.11
M3:EN-GATE: M3:R1.2, M3:U1.12
M3:GH-A: M3:Q1.4, M3:U1.43
M3:GH-B: M3:Q3.4, M3:U1.38
M3:GH-C: M3:Q5.4, M3:U1.33
M3:GL-A: M3:Q2.4, M3:U1.41
M3:GL-B: M3:Q4.4, M3:U1.36
M3:GL-C: M3:Q6.4, M3:U1.31
M3:GVDD: M3:C9.1, M3:U1.9
M3:PHASE-A: M3:C7.2, M3:J1.7, M3:Q3.1, M3:Q3.2, M3:Q3.3, M3:Q4.5678, M3:U1.37
M3:PHASE-B: M3:C6.2, M3:J1.8, M3:Q1.1, M3:Q1.2, M3:Q1.3, M3:Q2.5678, M3:U1.42
M3:PHASE-C: M3:C8.2, M3:J1.6, M3:Q5.1, M3:Q5.2, M3:Q5.3, M3:Q6.5678, M3:U1.32
M4-!CS: M4:U1.4, RN7.16
M4-A-H: M4:U1.15, RN7.15
M4-A-L: M4:U1.16, RN7.14
M4-B-H: M4:U1.13, RN4.16
M4-B-L: M4:U1.14, RN4.15
M4-C-H: M4:U1.17, RN7.13
M4-C-L: M4:U1.18, RN7.12
M4-ENC-A: M4:J2.2, RN4.14
M4-ENC-B: M4:J2.1, RN4.13
M4-H1: M4:J1.1, RN7.9
M4-H2: M4:J1.3, RN7.10
M4-H3: M4:J1.5, RN7.11
M4:+3.3V: M4:C1.1, M4:C10.1, M4:R1.1, M4:U1.19, M4:U1.20, M4:U1.45
M4:AVDD: M4:C2.1, M4:U1.23
M4:BST-A: M4:C6.1, M4:U1.44
M4:BST-B: M4:C7.1, M4:U1.39
M4:BST-C: M4:C8.1, M4:U1.34
M4:CP1: M4:C3.1, M4:U1.10
M4:CP2: M4:C3.2, M4:U1.11
M4:EN-GATE: M4:R1.2, M4:U1.12
M4:GH-A: M4:Q1.4, M4:U1.43
M4:GH-B: M4:Q3.4, M4:U1.38
M4:GH-C: M4:Q5.4, M4:U1.33
M4:GL-A: M4:Q2.4, M4:U1.41
M4:GL-B: M4:Q4.4, M4:U1.36
M4:GL-C: M4:Q6.4, M4:U1.31
M4:GVDD: M4:C9.1, M4:U1.9
M4:PHASE-A: M4:C7.2, M4:J1.7, M4:Q3.1, M4:Q3.2, M4:Q3.3, M4:Q4.5678, M4:U1.37
M4:PHASE-B: M4:C6.2, M4:J1.8, M4:Q1.1, M4:Q1.2, M4:Q1.3, M4:Q2.5678, M4:U1.42
M4:PHASE-C: M4:C8.2, M4:J1.6, M4:Q5.1, M4:Q5.2, M4:Q5.3, M4:Q6.5678, M4:U1.32
MISO: IR.1, J3.1, KIT1.P$5, U4.P$1
MISO-AUX: DD:U1.6, M1:U1.6, M2:U1.6, M3:U1.6, M4:U1.6, RN1.12, U2.14, U3.14
MISO-FPGA: KIT1.P$35, U1.44
MISO-RADIO: KIT1.P$28, RADIO.3
MOSI: IR.2, J3.2, KIT1.P$4, LED1.4, U4.P$14
MOSI-AUX: DD:U1.5, M1:U1.5, M2:U1.5, M3:U1.5, M4:U1.5, RN1.11, U2.13, U3.13
MOSI-FPGA: KIT1.P$36, U1.63
MOSI-RADIO: KIT1.P$27, RADIO.7
unnamed: F1.2, R26.1
unnamed: LED1.5, R30.2, U5.4
unnamed: C31.1, U4.P$7
unnamed: R32.2, U4.P$5
PWR-ERR: D6.C, U11.4, U12.4
R-P1: RN8.1, U1.82
R-P2: RN8.2, U1.81
R-P3: RN8.3, U1.77
R-P4: RN8.4, U1.76
R-P5: RN8.5, U1.75
R-P6: RN8.6, U1.74
R-P7: RN8.7, U1.70
R-P8: RN8.8, U1.68
R-P9: RN6.1, U1.91
R-P10: RN6.2, U1.89
R-P11: RN6.3, U1.88
R-P12: RN6.4, U1.87
R-P13: RN6.5, U1.86
R-P14: RN6.6, U1.85
R-P15: RN6.7, U1.84
R-P16: RN6.8, U1.83
R-P17: RN5.1, U1.101
R-P18: RN5.2, U1.98
R-P19: RN5.3, U1.97
R-P20: RN5.4, U1.96
R-P21: RN5.5, U1.95
R-P22: RN5.6, U1.94
R-P23: RN5.7, U1.93
R-P24: RN5.8, U1.92
R-P25: RN3.1, U1.117
R-P26: RN3.2, U1.116
R-P27: RN3.3, U1.113
R-P28: RN3.4, U1.112
R-P29: RN3.5, U1.106
R-P30: RN3.6, U1.105
R-P31: RN3.7, U1.104
R-P32: RN3.8, U1.103
R-P36: RN1.4, U1.125
R-P37: RN1.5, U1.124
R-P38: RN1.6, U1.123
R-P39: RN1.7, U1.122
R-P40: RN1.8, U1.119
R-P41: RN2.1, U1.5
R-P42: RN2.2, U1.4
R-P43: RN2.3, U1.3
R-P44: RN2.4, U1.2
R-P45: RN2.5, U1.142
R-P46: RN2.6, U1.141
R-P47: RN2.7, U1.140
R-P48: RN2.8, U1.139
R-P49: RN4.1, U1.21
R-P50: RN4.2, U1.20
R-P51: RN4.3, U1.17
R-P52: RN4.4, U1.16
R-P53: RN4.5, U1.15
R-P54: RN4.6, U1.14
R-P55: RN4.7, U1.8
R-P56: RN4.8, U1.7
R-P57: RN7.1, U1.35
R-P58: RN7.2, U1.34
R-P59: RN7.3, U1.32
R-P60: RN7.4, U1.31
R-P61: RN7.5, U1.26
R-P62: RN7.6, U1.25
R-P63: RN7.7, U1.24
R-P64: RN7.8, U1.23
SCK: IR.3, J3.3, KIT1.P$6, U4.P$13, U5.2
SCK-AUX: DD:U1.7, M1:U1.7, M2:U1.7, M3:U1.7, M4:U1.7, RN1.13, U2.15, U3.15
SCK-FPGA: KIT1.P$34, U1.71
SCK-RADIO: KIT1.P$29, RADIO.8
SCL: IC1.12, J4.4, KIT1.P$25, R7.1
SDA: IC1.13, J4.3, KIT1.P$26, R6.1
SENSE-BATT: C1.1, KIT1.P$33, R1.2, R2.1
SENSE-VIN: C2.1, KIT1.P$32, R3.2, R4.1
VBATT: J5.1, U8.1, U8.2, U8.3, U8.4, U8.5, U8.6, U8.7, U8.8, XF1.1, XF1.2
VDD-LED: D1.A, R5.2
VIN: J6.1, R13.2, U8.17

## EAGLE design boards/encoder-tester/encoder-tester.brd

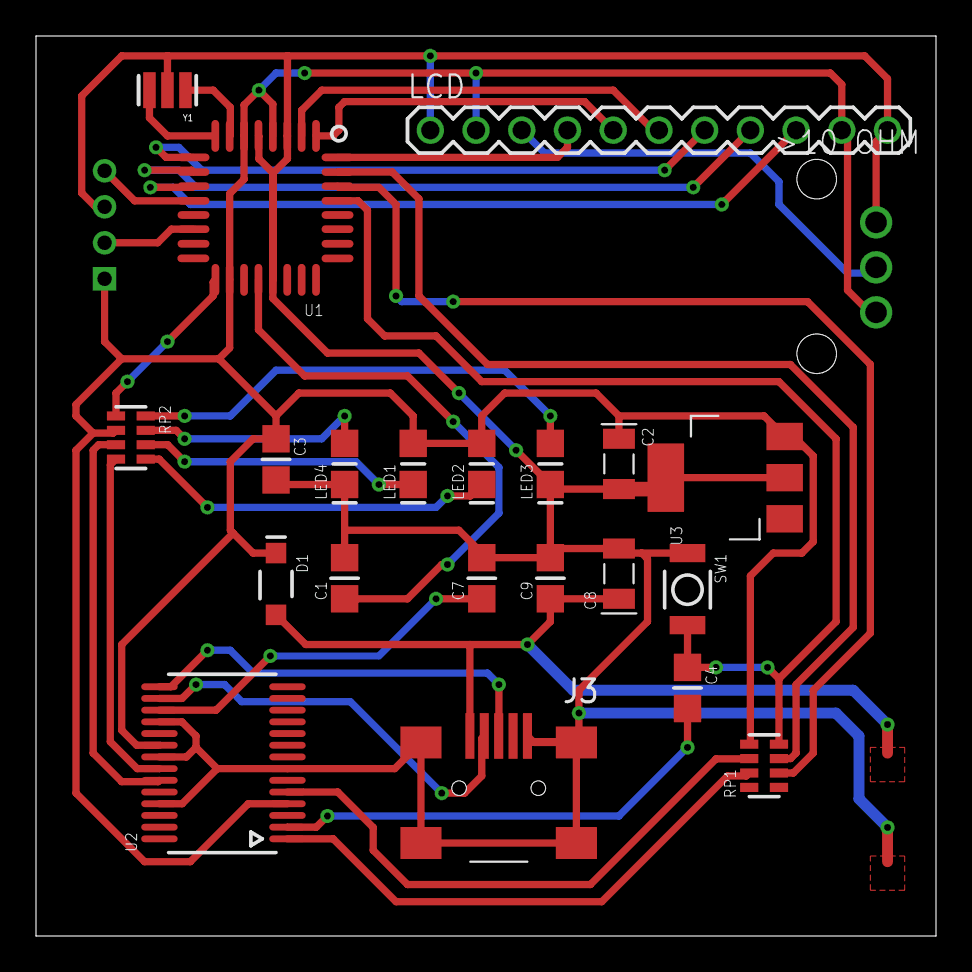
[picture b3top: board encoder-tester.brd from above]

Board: 2 copper layers, 50.0 x 50.0 mm, 23 parts (1 on the bottom side), 31 nets.

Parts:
C1, C3, C4, C7, C9: 0.1uF; CAP0805-NP
C2, C8: 4.7uF; TAN-A
D1: MBR0520; SOD-123
J3: USB-MINI-B%C; USB-MINI-B_2
J6: 2MM-4V; 2MM-4-V
LCD: M11PTH; 1X11
LED1: RED_RX; LED0805
LED2: GREEN_TX; LED0805
LED3: L_AMBER; LED0805
LED4: BLUE; LED0805
RP1: 1K; RES4NT
RP2: 330; RES4NT
SW1: RESET; 157SW
U1: ATMEGA168-20AU; QFP032
U2: FT232RL; SSOP28
U3: UA78M05; SOT223
U$7: 10OHMPOT; POTFOOT
Y1: 16MHz; RESONATOR

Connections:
3V3: C7.1, U2.17
+5V: C2.1, C3.1, D1.1, J6.1, LCD.2, LCD.10, LED1.2, LED2.2, RP1.5, RP2.2, U1.4, U1.6, U1.18, U2.4, U2.20, U3.3, U$7.1
AREF: C1.1, U1.20
COM: C1.2, C2.2, C3.2, C7.2, C8.2, C9.2, J3.1, J3.6, J3.7, J3.8, J3.9, J6.3, LCD.1, LCD.11, LED3.1, LED4.1, SW1.1, U1.3, U1.5, U1.21, U2.7, U2.18, U2.21, U2.25, U3.2, U3.4, U$7.3, Y1.2
D0/RX: RP1.2, U1.30
D1/TX: RP1.3, U1.31
D2: LCD.4, U1.32
D3: LCD.5, U1.1
D4: LCD.6, U1.2
D5: LCD.7, U1.9
D6: LCD.8, U1.10
D7: LCD.9, U1.11
D8: J6.4, U1.12
D10: J6.2, U1.14
D13/SCK: RP2.1, U1.17
unnamed: U1.8, Y1.3
unnamed: U1.7, Y1.1
unnamed: LED4.2, RP2.7
unnamed: C4.2, U2.2
unnamed: J3.3, U2.15
unnamed: J3.4, U2.16
unnamed: LED3.2, RP2.8
unnamed: RP2.3, U2.23
unnamed: RP2.4, U2.22
unnamed: LED1.1, RP2.6
unnamed: LED2.1, RP2.5
POT: LCD.3, U$7.2
RESET: C4.1, RP1.4, SW1.2, U1.29
RX: RP1.7, U2.1
TX: RP1.6, U2.5
VUSB: C8.1, C9.1, D1.2, J3.5

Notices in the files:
parts and their libraries:
SparkFun-IC-Logic: Licensing: Creative Commons ShareAlike 4.0 International - https://creativecommons.org/licenses/by-sa/4.0
